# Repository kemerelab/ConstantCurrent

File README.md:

# ConstantCurrent
Circuits for driving constant current stimulators for electrical biphasic pulses and diodes.

### Currently in Prototyping stage

1. 3A LED driver.
2. Constant current biphasic pulses using low power op amps.

### Goals

1. Integrate with https://github.com/kemerelab/pi-stimserver project.

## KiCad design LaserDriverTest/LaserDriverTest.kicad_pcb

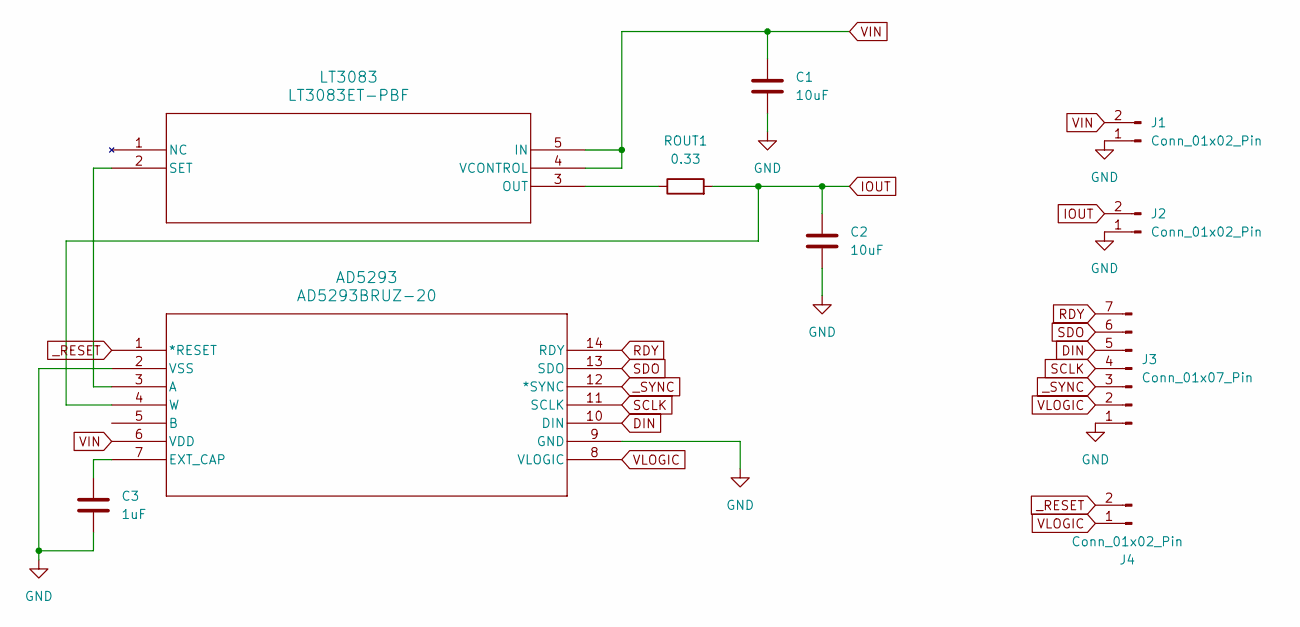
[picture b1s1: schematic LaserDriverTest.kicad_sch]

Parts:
AD5293: AD5293BRUZ-20; RU_14_ADI
C1, C2: 10uF; C_1206_3216Metric
C3: 1uF; C_1206_3216Metric
J1, J2, J4: Conn_01x02_Pin; PinHeader_1x02_P2.54mm_Vertical
J3: Conn_01x07_Pin; PinHeader_1x07_P2.54mm_Vertical
LT3083: LT3083ET-PBF; TO220-5_T
ROUT1: 0.33; R_4020_10251Metric

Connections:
DIN: AD5293.10 (DIN), J3.5
GND: AD5293.2 (VSS), AD5293.9 (GND), C1.2, C2.2, C3.2, J1.1, J2.1, J3.1
IOUT: AD5293.4 (W), C2.1, J2.2, ROUT1.2
unnamed: AD5293.3 (A), LT3083.2 (SET)
unnamed: AD5293.7 (EXT_CAP), C3.1
unnamed: LT3083.3 (OUT), ROUT1.1
RDY: AD5293.14 (RDY), J3.7
SCLK: AD5293.11 (SCLK), J3.4
SDO: AD5293.13 (SDO), J3.6
VIN: AD5293.6 (VDD), C1.1, J1.2, LT3083.4 (VCONTROL), LT3083.5 (IN)
VLOGIC: AD5293.8 (VLOGIC), J3.2, J4.1
_RESET: AD5293.1 (*RESET), J4.2
_SYNC: AD5293.12 (*SYNC), J3.3

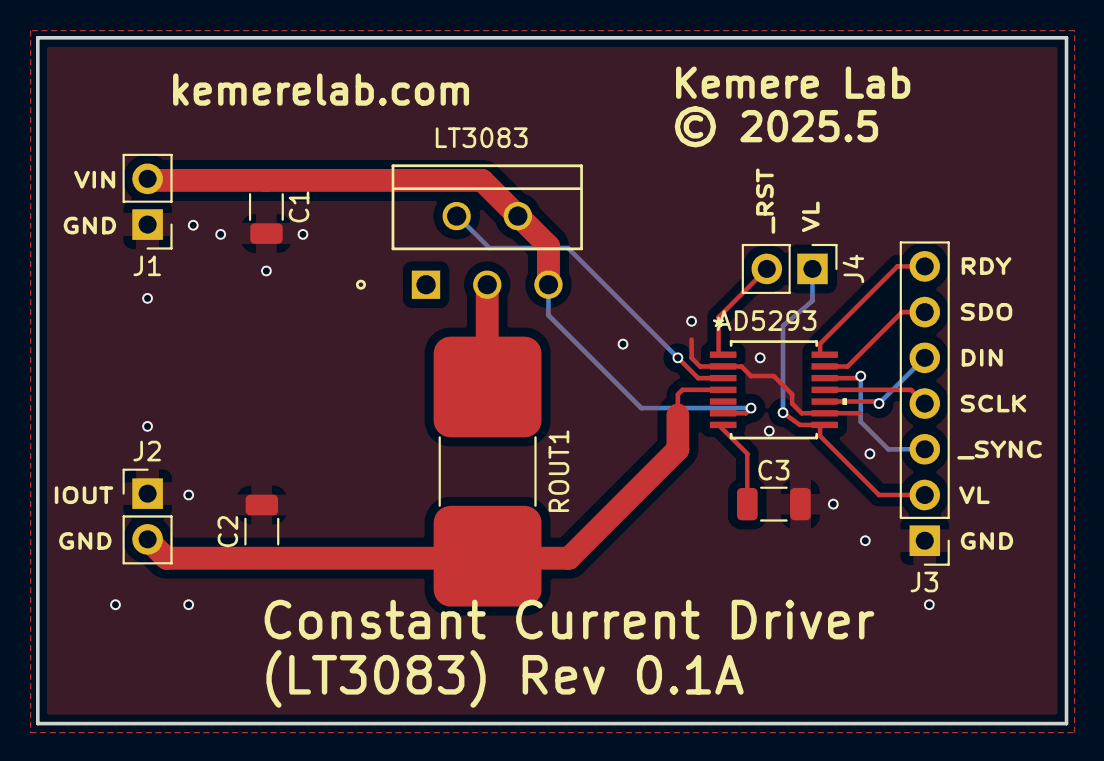
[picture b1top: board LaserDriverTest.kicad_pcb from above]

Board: 2 copper layers, 57.1 x 38.1 mm, 10 parts (0 on the bottom side), 13 nets.

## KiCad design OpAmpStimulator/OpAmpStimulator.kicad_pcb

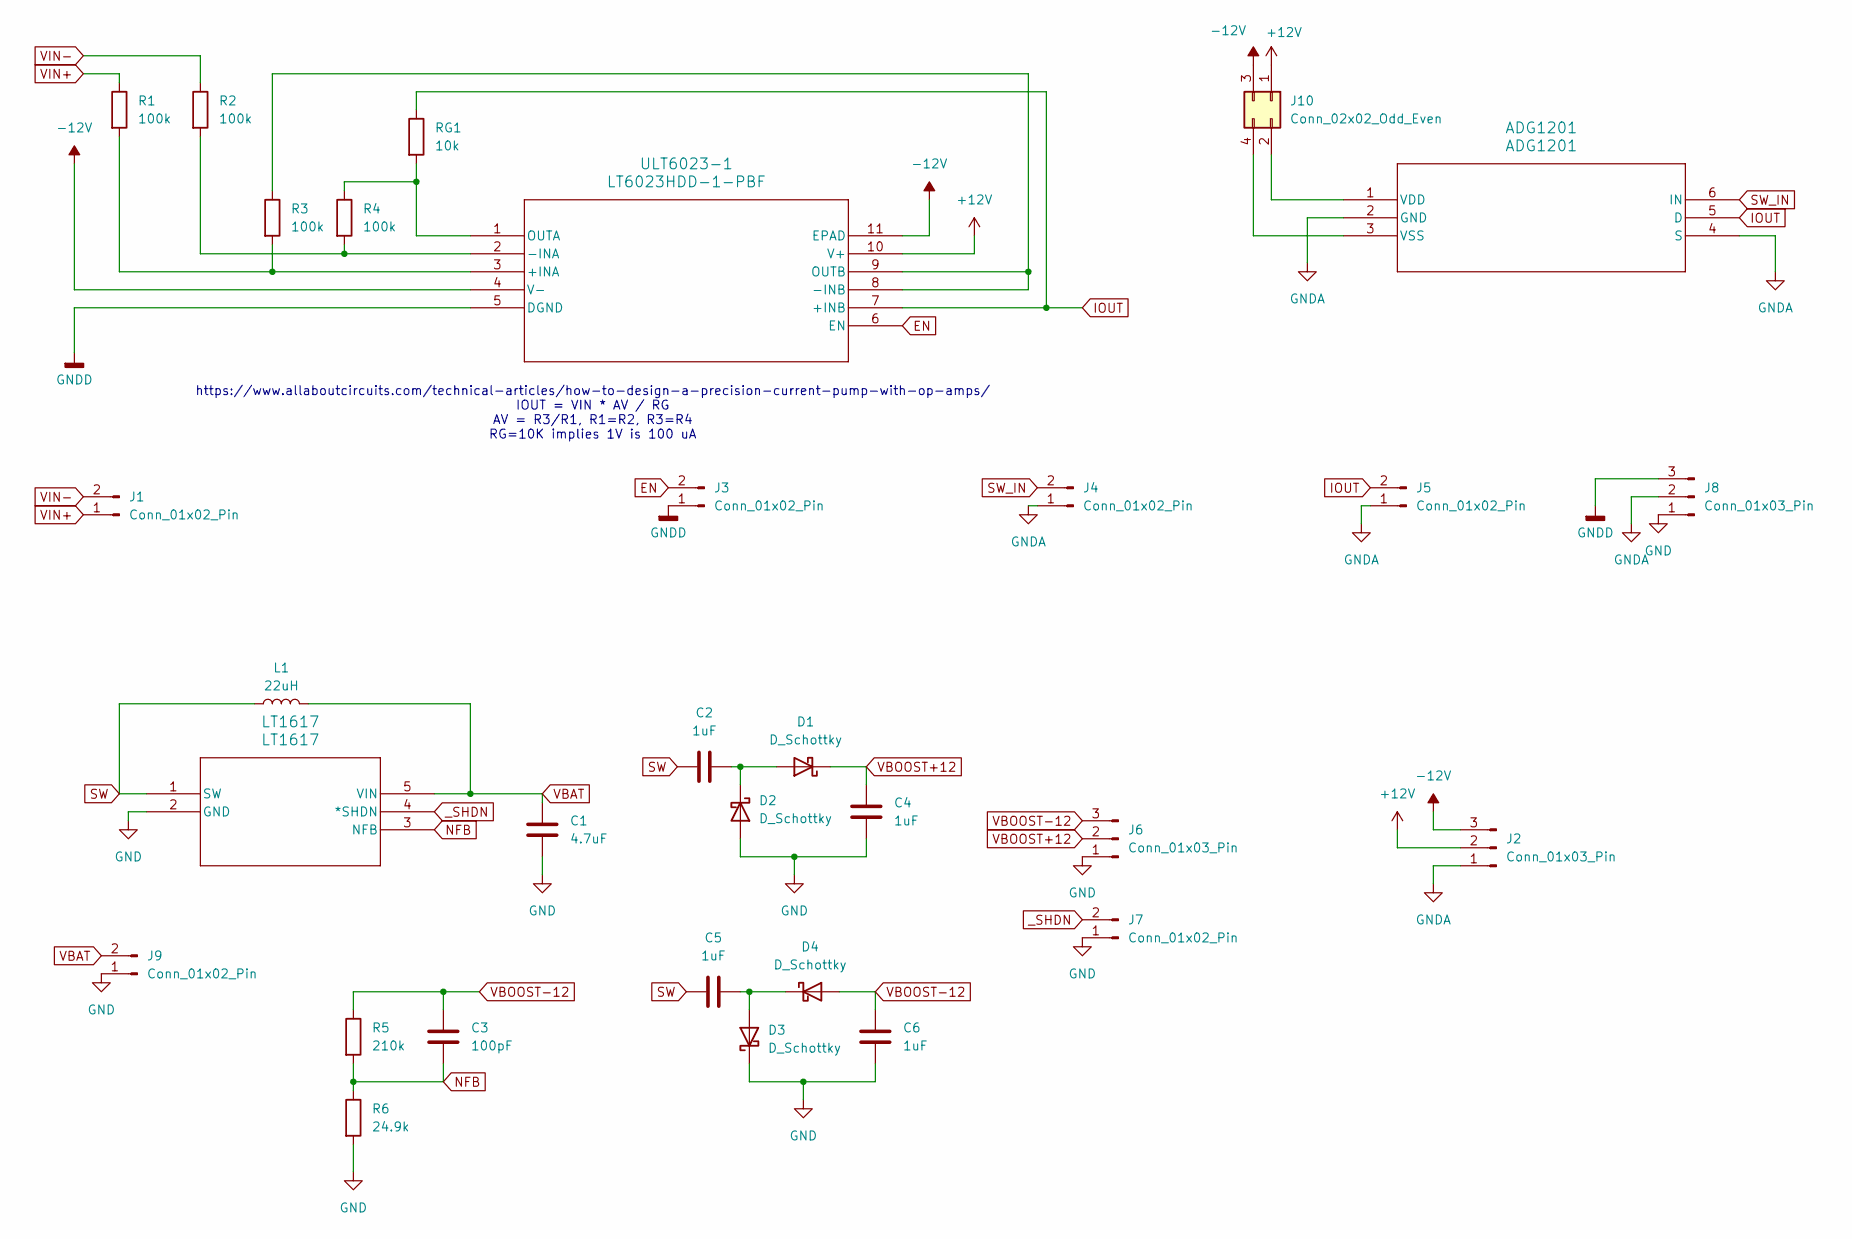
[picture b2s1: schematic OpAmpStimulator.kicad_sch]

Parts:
ADG1201: ADG1201; RJ_6_ADI
C1: 4.7uF; C_0805_2012Metric
C2, C4, C5, C6: 1uF; C_0603_1608Metric
C3: 100pF; C_0603_1608Metric
D1, D2, D3, D4: D_Schottky; D_0805_2012Metric
J1, J3, J4, J5, J7, J9: Conn_01x02_Pin; PinHeader_1x02_P2.54mm_Vertical
J2, J6, J8: Conn_01x03_Pin; PinHeader_1x03_P2.54mm_Vertical
J10: Conn_02x02_Odd_Even; PinHeader_2x02_P2.54mm_Vertical
L1: 22uH; L_1210_3225Metric
LT1617: LT1617; S_5_ADI
R1, R2, R3, R4: 100k; R_0805_2012Metric
R5: 210k; R_0603_1608Metric
R6: 24.9k; R_0603_1608Metric
RG1: 10k; R_0805_2012Metric
ULT6023-1: LT6023HDD-1-PBF; DFN-10_DD_LIT

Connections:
+12V: J2.2, J10.1, ULT6023-1.10 (V+)
-12V: J2.3, J10.3, ULT6023-1.4 (V-), ULT6023-1.11 (EPAD)
EN: J3.2, ULT6023-1.6 (EN)
GND: C1.1, C4.2, C6.2, D2.2 (A), D3.1 (K), J6.1, J7.1, J8.1, J9.1, LT1617.2 (GND), R6.2
GNDA: ADG1201.2 (GND), ADG1201.4 (S), J2.1, J4.1, J5.1, J8.2
GNDD: J3.1, J8.3, ULT6023-1.5 (DGND)
IOUT: ADG1201.5 (D), J5.2, RG1.1, ULT6023-1.7 (+INB)
NFB: C3.2, LT1617.3 (NFB), R5.2, R6.1
unnamed: ADG1201.1 (VDD), J10.2
unnamed: ADG1201.3 (VSS), J10.4
unnamed: C2.2, D1.2 (A), D2.1 (K)
unnamed: C5.2, D3.2 (A), D4.1 (K)
unnamed: R1.2, R3.2, ULT6023-1.3 (+INA)
unnamed: R2.2, R4.2, ULT6023-1.2 (-INA)
unnamed: R3.1, ULT6023-1.8 (-INB), ULT6023-1.9 (OUTB)
unnamed: R4.1, RG1.2, ULT6023-1.1 (OUTA)
SW: C2.1, C5.1, L1.1, LT1617.1 (SW)
SW_IN: ADG1201.6 (IN), J4.2
VBAT: C1.2, J9.2, L1.2, LT1617.5 (VIN)
VBOOST+12: C4.1, D1.1 (K), J6.2
VBOOST-12: C3.1, C6.1, D4.2 (A), J6.3, R5.1
VIN+: J1.1, R1.1
VIN-: J1.2, R2.1
_SHDN: J7.2, LT1617.4 (*SHDN)

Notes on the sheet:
https://www.allaboutcircuits.com/technical-articles/how-to-design-a-precision-current-pump-with-op-amps/ IOUT = VIN * AV / RG AV = R3/R1, R1=R2, R3=R4 RG=10K implies 1V is 100 uA

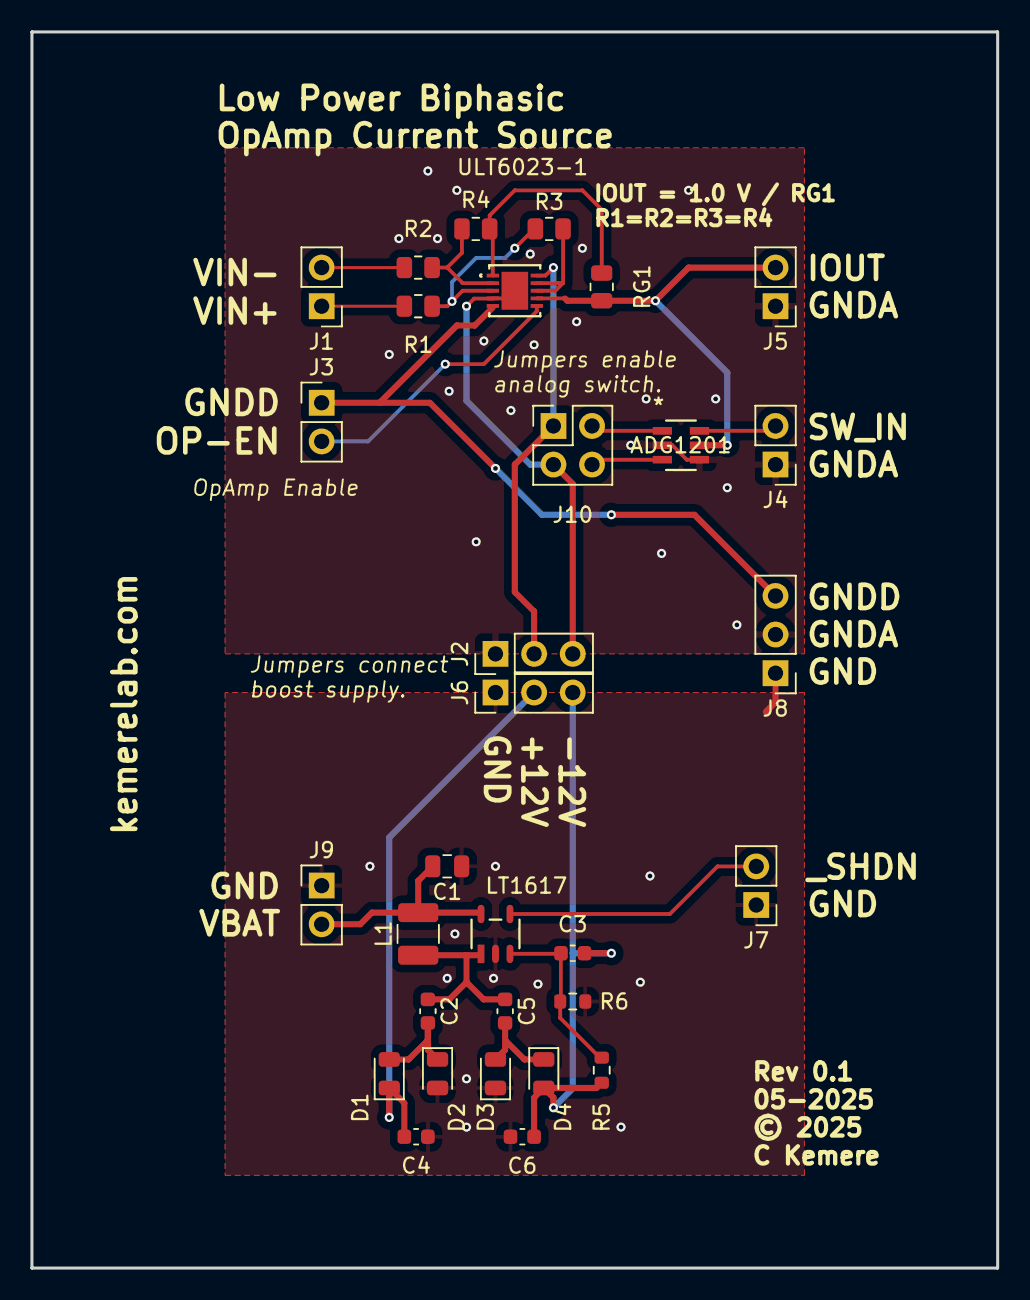
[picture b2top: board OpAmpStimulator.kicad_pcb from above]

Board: 2 copper layers, 63.5 x 81.3 mm, 31 parts (0 on the bottom side), 24 nets.

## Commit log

2025-05-15 Updated with product links
2025-05-30 Added LTSpice simulations

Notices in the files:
LaserDriverTest/LaserDriverTest.kicad_pcb:
©️ 2025.5
OpAmpStimulator/OpAmpStimulator.kicad_pcb:
© 2025
